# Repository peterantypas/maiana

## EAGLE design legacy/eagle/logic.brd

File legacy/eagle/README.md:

# Eagle CAD files

The hardware is made up of two boards. Although I officially baptised them the "Logic Stage" and the "RF Stage", I think it's better to think of them
as the "easy" board and the "tricky" board. 

The "easy" board holds the microcontroller (STM32F302, an ARM Cortex M4 running at 72Mhz), the USB interface, power regulator, EEPROM and GPS. It carries nothing
more than power and digital signals. No analog RF signal traverses any trace on it.

The "tricky" board, is effectively a mixed signal circuit. It holds the RF ICs (which share the same SPI bus), the LNA, the Front End Module and the associated 
analog filters. The critical RF traces are designed as coplanar waveguides with liberal quantities of via stitches, and they should be close to 50Ohm for 
Oshpark's 2-layer PCB and dialectric.

The two dual-layer PCBs are mirror images of each other and they mate with standard .01" male/female pins. Unlike Arduino and Pi hats, the boards mate 
"back-to-back", so as to maximize isolation between the MCU and the RF traces.

I chose to partition the hardware in this way to minimize the pain of iterating, since the analog RF stage went (and will continue to go) 
through more iterations than the MCU / EEPROM / GPS stage.

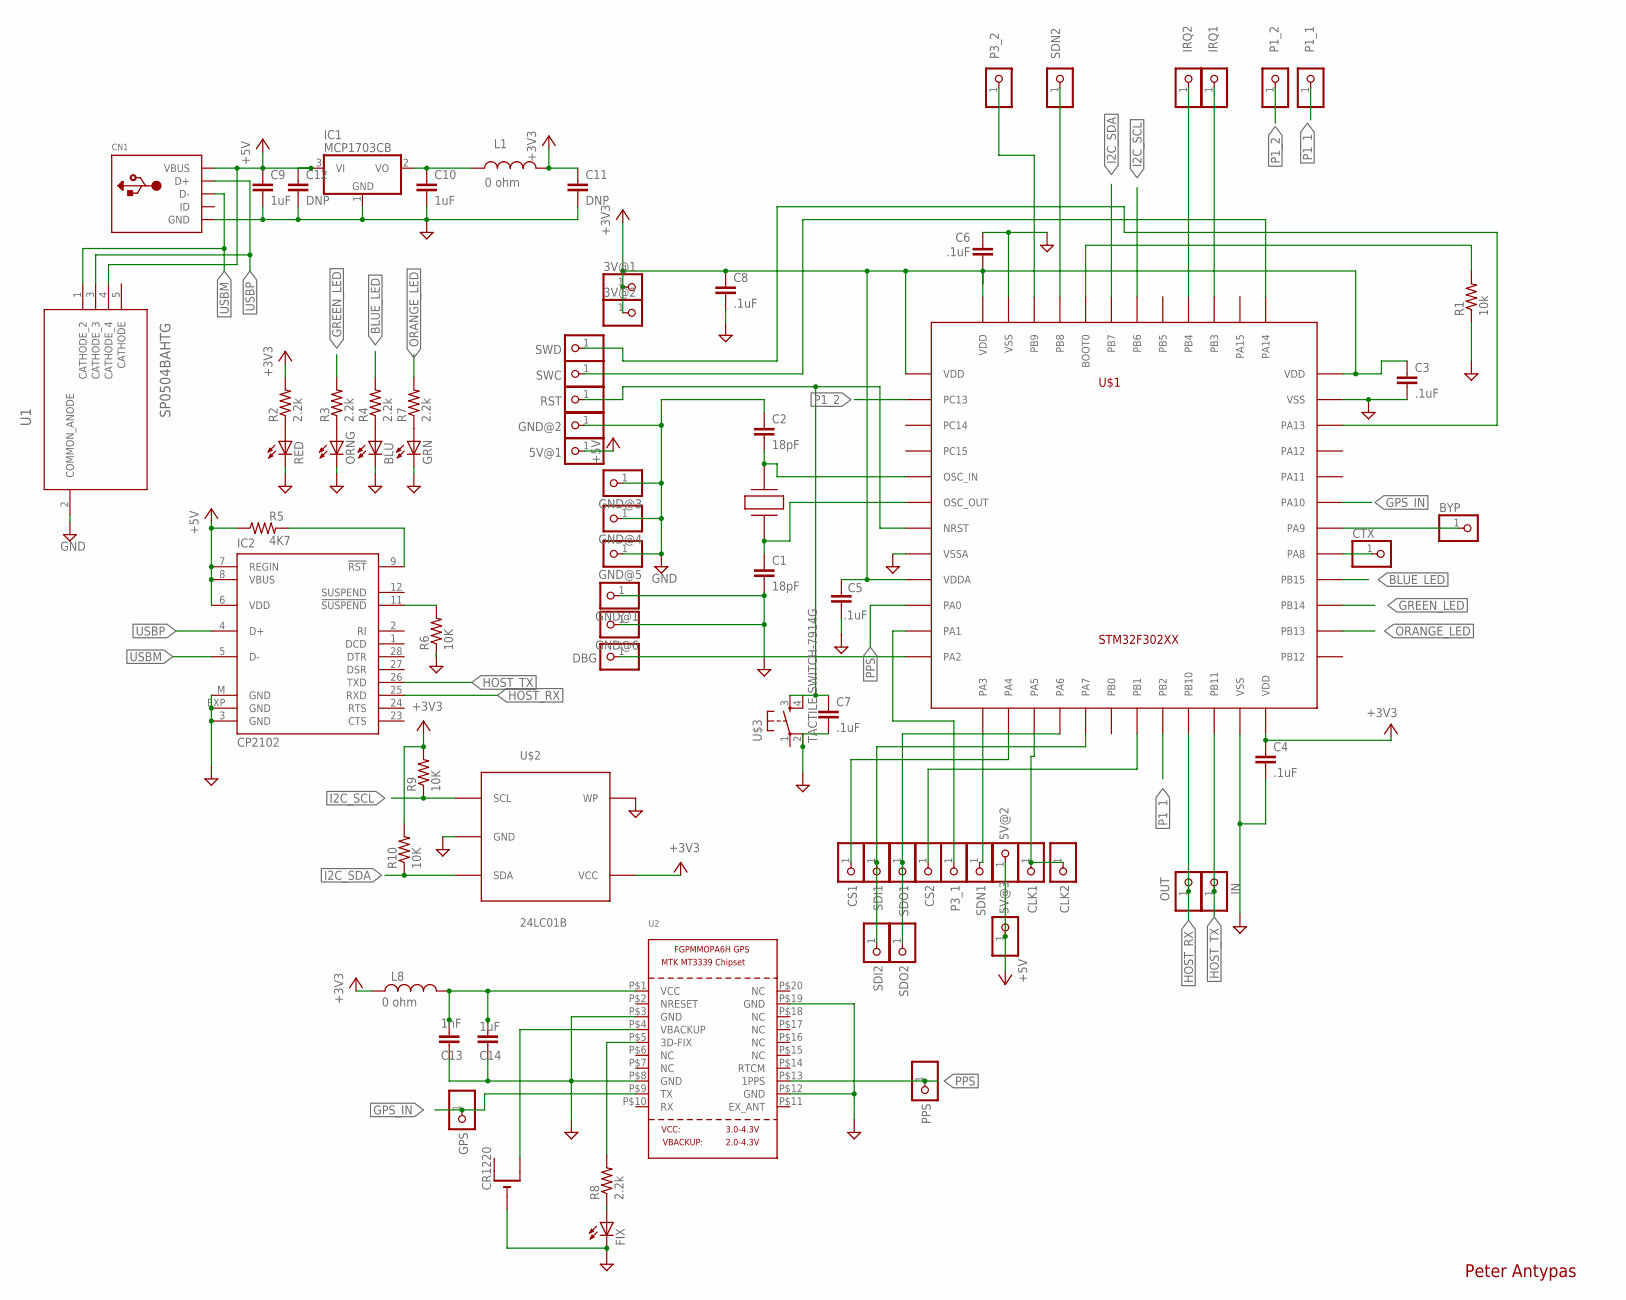
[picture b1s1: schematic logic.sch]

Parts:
3V@1, 3V@2, 5V@1, 5V@2, 5V@3: PINHD-1X1; 1X01
BLU: LEDCHIP-LED0603; CHIP-LED0603
BYP: PINHD-1X1; 1X01
C1, C2: 18pF; 0603-CAP
C3, C4, C5, C6, C7, C8: .1uF; 0603-CAP
C9, C10: 1uF; 0805
C11, C12: DNP; 0603-CAP
C13: 1nF; 0603-CAP
C14: 1uF; 0603-CAP
CLK1, CLK2: PINHD-1X1; 1X01
CN1: USBMINIB; USB-MINIB
CR1220: CR1220SMT; CR1220-SMD
CS1, CS2: PINHD-1X1; 1X01
CTX: PINHD-1X1; 1X01
DBG: PINHD-1X1; 1X01
FIX: LEDCHIP-LED0603; CHIP-LED0603
GND@1, GND@2, GND@3, GND@4, GND@5, GND@6: PINHD-1X1; 1X01
GPS: PINHD-1X1; 1X01
GRN: LEDCHIP-LED0603; CHIP-LED0603
IC1: MCP1703CB; SOT23
IC2: CP2102; MLP28
IN: PINHD-1X1; 1X01
IRQ1, IRQ2: PINHD-1X1; 1X01
L1, L8: 0 ohm; 0603
ORNG: LEDCHIP-LED0603; CHIP-LED0603
OUT: PINHD-1X1; 1X01
P1_1, P1_2, P3_1, P3_2: PINHD-1X1; 1X01
PPS: PINHD-1X1; 1X01
R1: 10k; 0603-RES
R2, R3, R4, R7, R8: 2.2k; 0603-RES
R5: 4K7; 0603-RES
R6, R9, R10: 10K; 0603-RES
RED: LEDCHIP-LED0603; CHIP-LED0603
RST: PINHD-1X1; 1X01
SDI1, SDI2: PINHD-1X1; 1X01
SDN1, SDN2: PINHD-1X1; 1X01
SDO1, SDO2: PINHD-1X1; 1X01
SWC: PINHD-1X1; 1X01
SWD: PINHD-1X1; 1X01
U1: SP0504BAHTG; SOT95P280X145-5N
U2: GPS_FGPMMOPA6H; FGPMMOPA6H
U$1: STM32F302XX; LQFP48
U$2: 24LC01B; SOT23-5
U$3: TACTILE-SWITCH-7914G; 7914G
X1: TXC_7A

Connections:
+3V3: 3V@1.1, 3V@2.1, C3.1, C4.1, C5.2, C6.1, C8.1, C11.1, L1.2, L8.1, R2.2, R9.2, R10.2, U$1.P$1 (VDD), U$1.P$9 (VDDA), U$1.P$24 (VDD), U$1.P$36 (VDD), U$1.P$48 (VDD), U$2.4 (VCC)
+5V: 5V@1.1, 5V@2.1, 5V@3.1, C9.1, C12.1, CN1.VBUS, IC1.3 (VI), IC2.6 (VDD), IC2.7 (REGIN), IC2.8 (VBUS), R5.1, U1.4 (CATHODE_4)
BLUE_LED: R4.2, U$1.P$28 (PB15)
EEPROM_CS: C7.1, RST.1, U$1.P$7 (NRST), U$3.3
GND: BLU.C, C1.2, C2.1, C3.2, C4.2, C5.1, C6.2, C7.2, C8.2, C9.2, C10.2, C11.2, C12.2, C13.2, C14.2, CN1.GND, CR1220.-, FIX.C, GND@1.1, GND@2.1, GND@3.1, GND@4.1, GND@5.1, GND@6.1, GRN.C, IC1.1 (GND), IC2.3 (GND), IC2.EXP (GND), IC2.M (GND), ORNG.C, R1.1, R6.1, U1.2 (COMMON_ANODE), U2.P$3 (GND), U2.P$8 (GND), U2.P$12 (GND), U2.P$19 (GND), U$1.P$8 (VSSA), U$1.P$23 (VSS), U$1.P$35 (VSS), U$1.P$47 (VSS), U$2.2 (GND), U$2.5 (WP), U$3.2
GPS_IN: GPS.1, U2.P$9 (TX), U$1.P$31 (PA10)
GREEN_LED: R3.2, U$1.P$27 (PB14)
HOST_RX: IC2.25 (RXD), OUT.1, U$1.P$21 (PB10)
HOST_TX: IC2.26 (TXD), IN.1, U$1.P$22 (PB11)
I2C_SCL: R9.1, U$1.P$42 (PB6), U$2.1 (SCL)
I2C_SDA: R10.1, U$1.P$43 (PB7), U$2.3 (SDA)
unnamed: SDN2.1, U$1.P$45 (PB8)
unnamed: P3_1.1, U$1.P$11 (PA1)
unnamed: C10.1, IC1.2 (VO), L1.1
unnamed: R1.2, U$1.P$44 (BOOT0)
unnamed: SWC.1, U$1.P$37 (PA14)
unnamed: SDN1.1, U$1.P$13 (PA3)
unnamed: SWD.1, U$1.P$34 (PA13)
unnamed: IRQ1.1, U$1.P$39 (PB3)
unnamed: C2.2, U$1.P$5 (OSC_IN), X1.P$2
unnamed: CS1.1, U$1.P$14 (PA4)
unnamed: IRQ2.1, U$1.P$40 (PB4)
unnamed: FIX.A, R8.1
unnamed: CS2.1, U$1.P$19 (PB1)
unnamed: DBG.1, U$1.P$12 (PA2)
unnamed: P3_2.1, U$1.P$46 (PB9)
unnamed: R2.1, RED.A
unnamed: ORNG.A, R3.1
unnamed: C1.1, U$1.P$6 (OSC_OUT), X1.P$1
unnamed: BLU.A, R4.1
unnamed: CTX.1, U$1.P$29 (PA8)
unnamed: IC2.9 (!RST), R5.2
unnamed: IC2.11 (!SUSPEND), R6.2
unnamed: GRN.A, R7.1
unnamed: BYP.1, U$1.P$30 (PA9)
unnamed: R8.2, U2.P$5 (3D-FIX)
unnamed: CR1220.+$2 (+1), U2.P$4 (VBACKUP)
ORANGE_LED: R7.2, U$1.P$26 (PB13)
P1_1: P1_1.1, U$1.P$20 (PB2)
P1_2: P1_2.1, U$1.P$2 (PC13)
PPS: PPS.1, U2.P$13 (1PPS), U$1.P$10 (PA0)
PWR: RED.C
SDI: SDI1.1, SDI2.1, U$1.P$17 (PA7)
SDO: SDO1.1, SDO2.1, U$1.P$16 (PA6)
SPI_CLK: CLK1.1, CLK2.1, U$1.P$15 (PA5)
USBM: CN1.D-, IC2.5 (D-), U1.1 (CATHODE_2)
USBP: CN1.D+, IC2.4 (D+), U1.3 (CATHODE_3)
VDD1: C13.1, C14.1, L8.2, U2.P$1 (VCC)

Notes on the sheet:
Peter Antypas

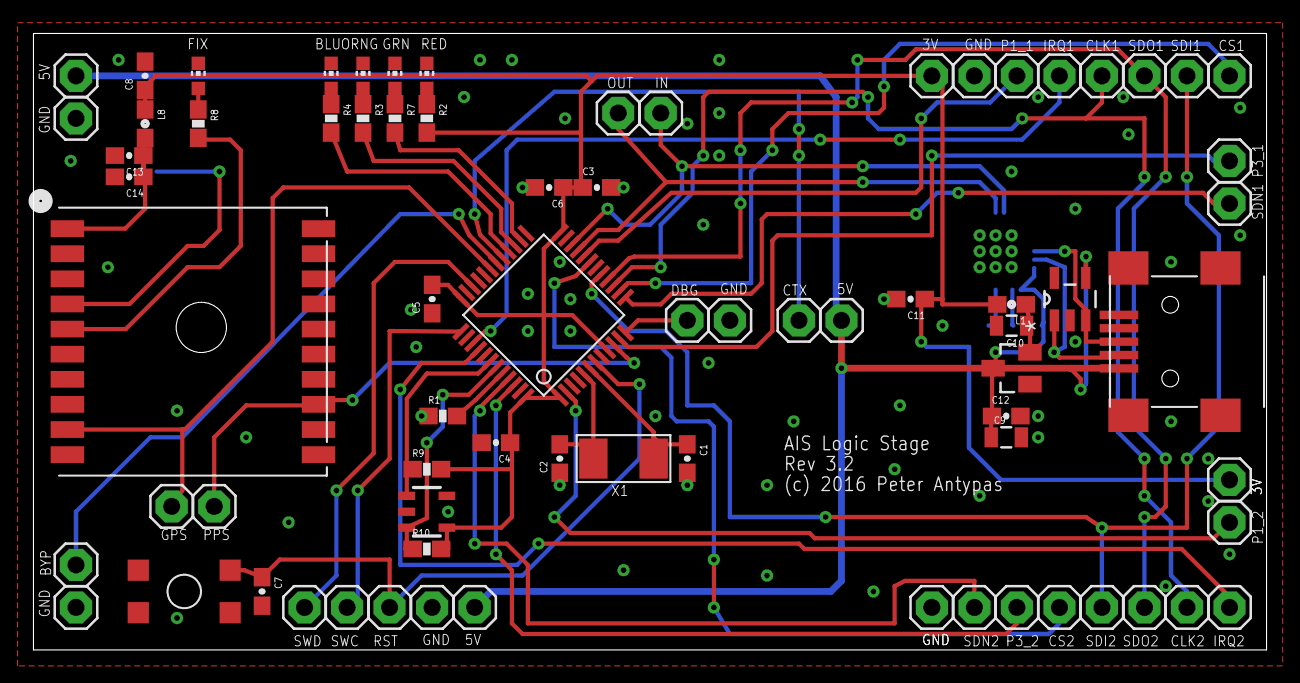
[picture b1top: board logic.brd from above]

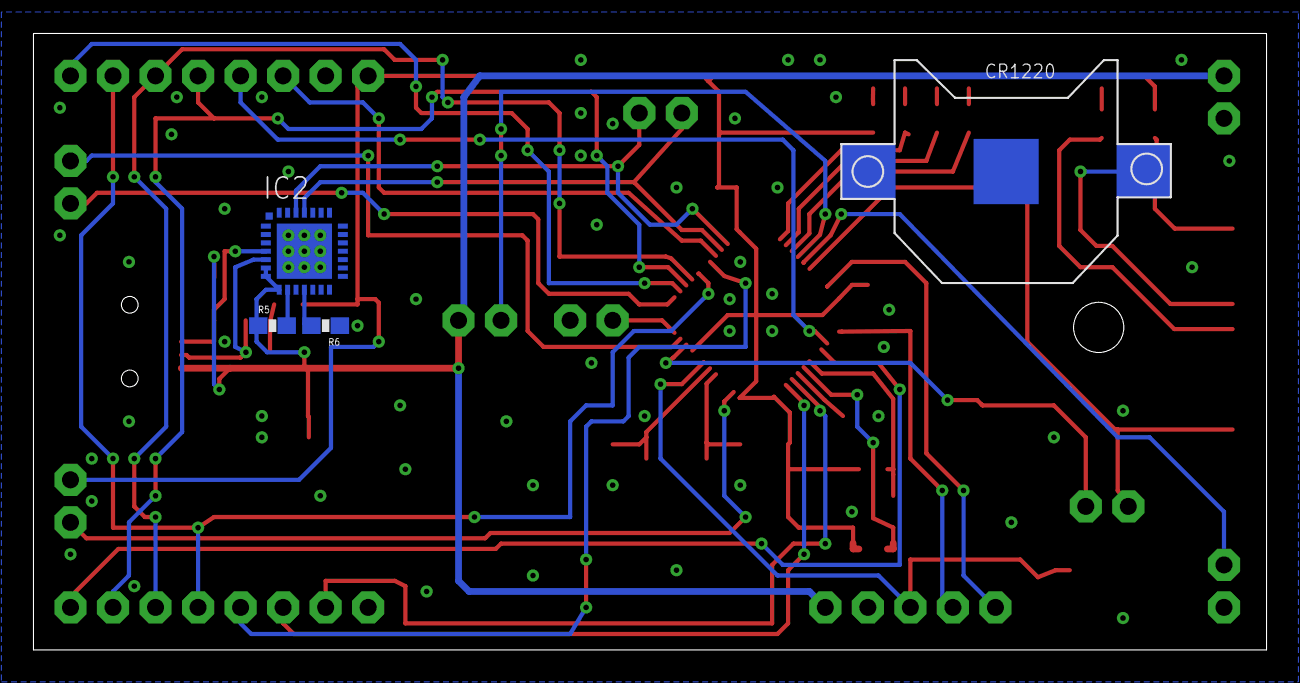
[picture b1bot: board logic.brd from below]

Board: 2 copper layers, 73.6 x 36.8 mm, 78 parts (4 on the bottom side), 47 nets.

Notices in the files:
legacy/eagle/logic.brd:
(c) 2016 Peter Antypas
parts and their libraries:
SparkFun-Capacitors: Licensing: Creative Commons ShareAlike 4.0 International - https://creativecommons.org/licenses/by-sa/4.0
